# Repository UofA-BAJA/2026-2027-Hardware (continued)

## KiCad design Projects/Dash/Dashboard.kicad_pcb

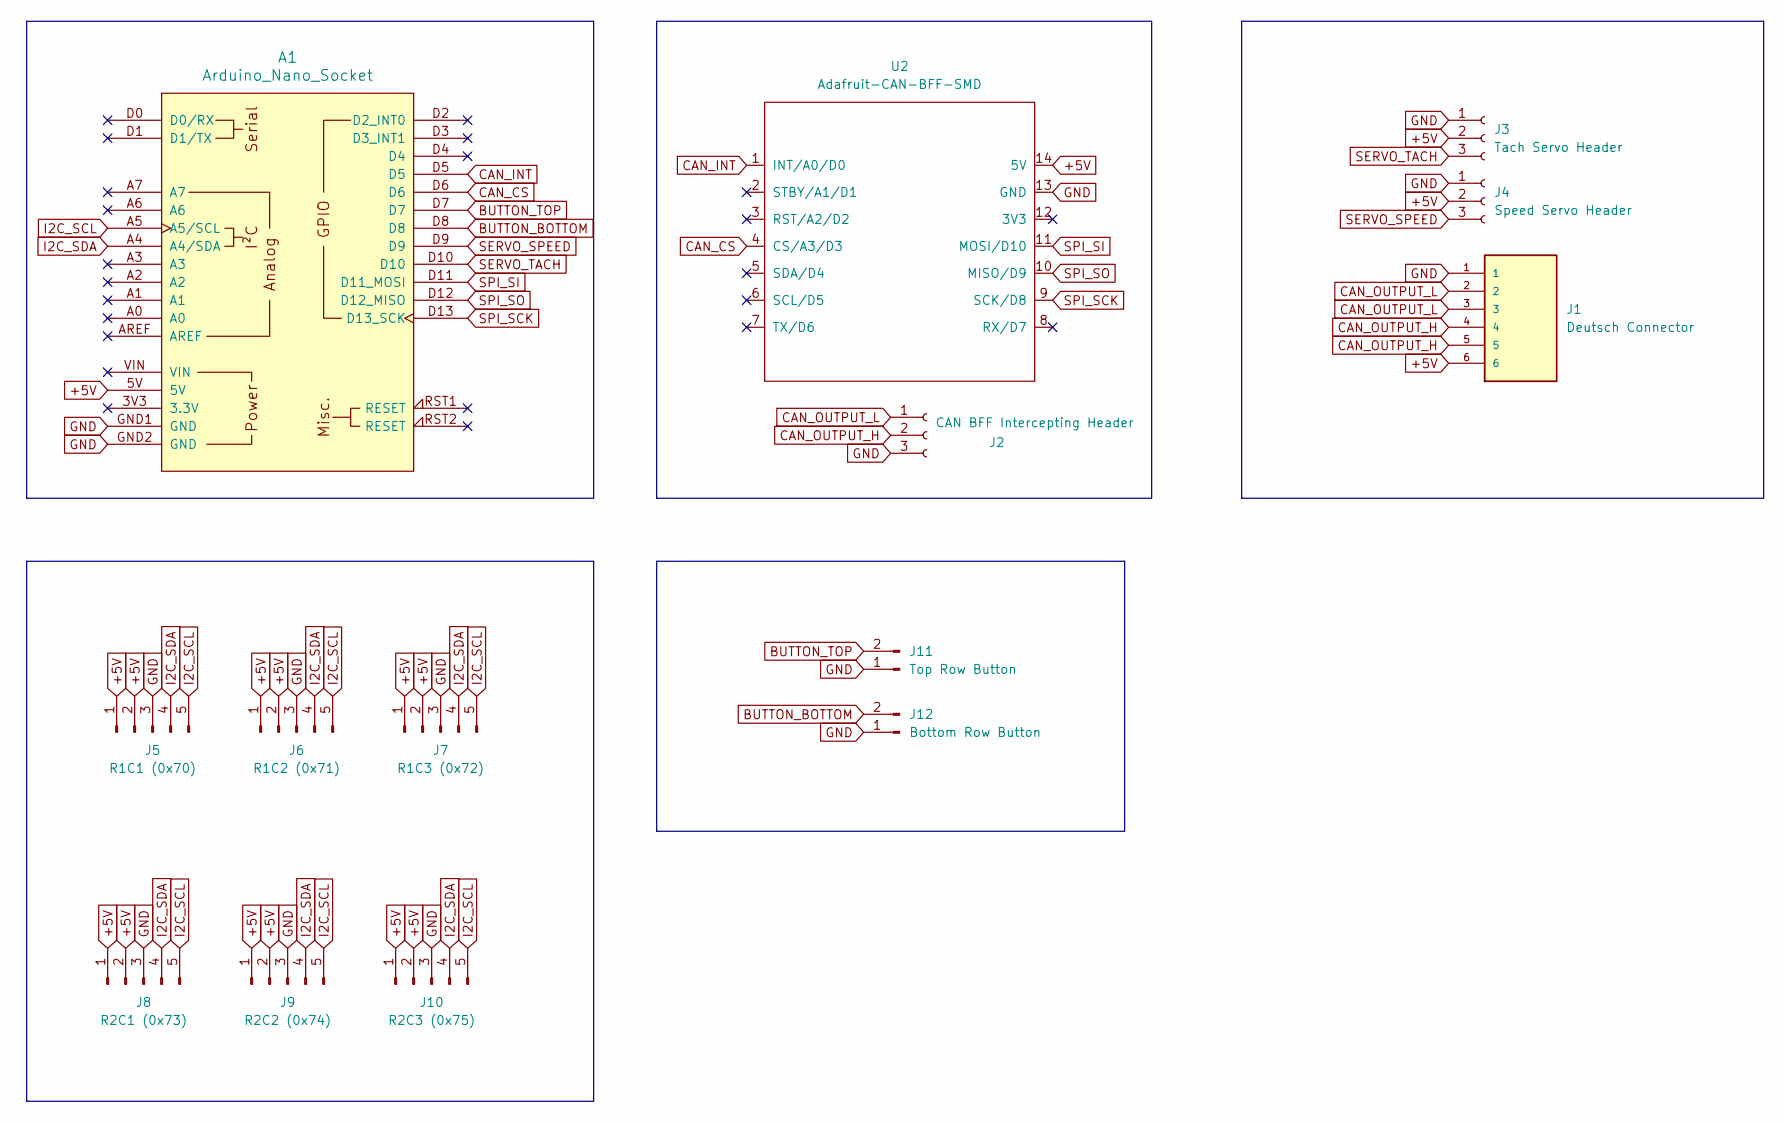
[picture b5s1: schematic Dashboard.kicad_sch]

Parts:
A1: Arduino_Nano_Socket
J1: Deutsch Connector; TE_DTF13-6P; PARTREV B
J2: CAN BFF Intercepting Header; PinHeader_1x03_P2.54mm_Vertical
J3: Tach Servo Header; PinHeader_1x03_P2.54mm_Vertical
J4: Speed Servo Header; PinHeader_1x03_P2.54mm_Vertical
J5: R1C1 (0x70); PinHeader_1x05_P2.54mm_Vertical
J6: R1C2 (0x71); PinHeader_1x05_P2.54mm_Vertical
J7: R1C3 (0x72); PinHeader_1x05_P2.54mm_Vertical
J8: R2C1 (0x73); PinHeader_1x05_P2.54mm_Vertical
J9: R2C2 (0x74); PinHeader_1x05_P2.54mm_Vertical
J10: R2C3 (0x75); PinHeader_1x05_P2.54mm_Vertical
J11: Top Row Button; PinHeader_1x02_P2.54mm_Vertical
J12: Bottom Row Button; PinHeader_1x02_P2.54mm_Vertical
U2: Adafruit-CAN-BFF-SMD

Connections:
+5V: A1.5V, J1.6, J3.2, J4.2, J5.1, J5.2, J6.1, J6.2, J7.1, J7.2, J8.1, J8.2, J9.1, J9.2, J10.1, J10.2, U2.14 (5V)
BUTTON_BOTTOM: A1.D8, J12.2
BUTTON_TOP: A1.D7, J11.2
CAN_CS: A1.D6, U2.4 (CS/A3/D3)
CAN_INT: A1.D5, U2.1 (INT/A0/D0)
CAN_OUTPUT_H: J1.4, J1.5, J2.2
CAN_OUTPUT_L: J1.2, J1.3, J2.1
GND: A1.GND1 (GND), A1.GND2 (GND), J1.1, J2.3, J3.1, J4.1, J5.3, J6.3, J7.3, J8.3, J9.3, J10.3, J11.1, J12.1, U2.13 (GND)
I2C_SCL: A1.A5 (A5/SCL), J5.5, J6.5, J7.5, J8.5, J9.5, J10.5
I2C_SDA: A1.A4 (A4/SDA), J5.4, J6.4, J7.4, J8.4, J9.4, J10.4
SERVO_SPEED: A1.D9, J4.3
SERVO_TACH: A1.D10, J3.3
SPI_SCK: A1.D13 (D13_SCK), U2.9 (SCK/D8)
SPI_SI: A1.D11 (D11_MOSI), U2.11 (MOSI/D10)
SPI_SO: A1.D12 (D12_MISO), U2.10 (MISO/D9)

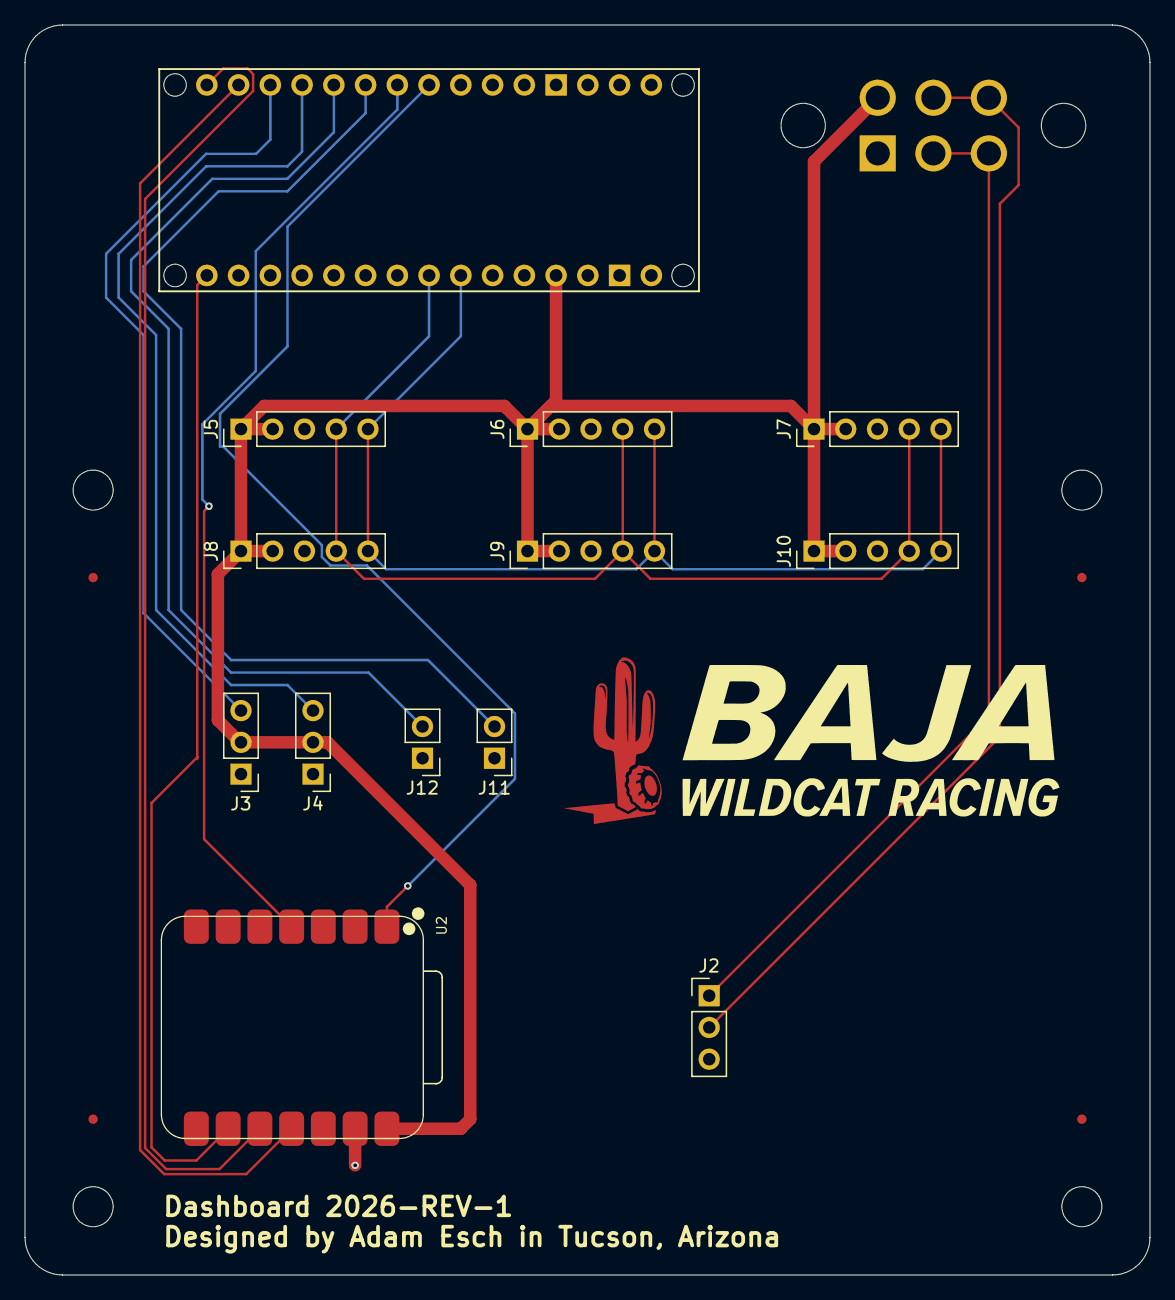
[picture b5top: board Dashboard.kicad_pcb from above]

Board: 2 copper layers, 90.0 x 100.0 mm, 14 parts (1 on the bottom side), 15 nets.

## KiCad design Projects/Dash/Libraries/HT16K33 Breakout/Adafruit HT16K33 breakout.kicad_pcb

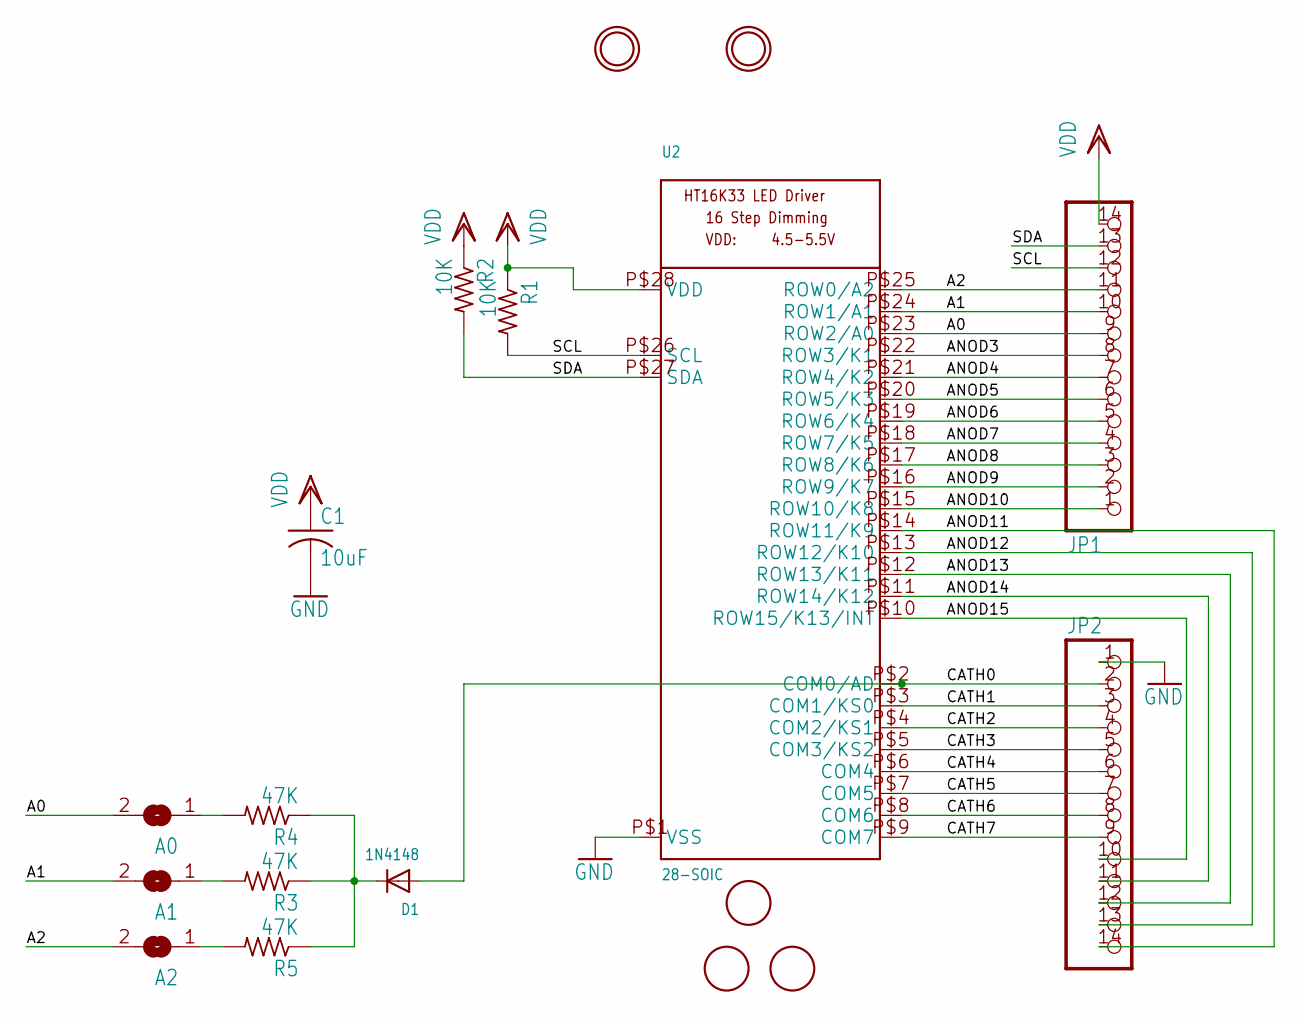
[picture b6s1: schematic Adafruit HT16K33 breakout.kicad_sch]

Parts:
A0, A1, A2: SOLDERJUMPERREFLOW_NOPASTE; SOLDERJUMPER_REFLOW_NOPASTE
C1: 10uF; C0805
D1: 1N4148; SOD-323F
JP1, JP2: PINHD-1X14-CB; 1X14-CB
R1, R2: 10K; R0805
R3, R4, R5: 47K; R0805
U2: 28-SOIC; SOP28_300MIL
U$1, U$2, U$6: FIDUCIAL; FIDUCIAL_1MM
U$4, U$5: MOUNTINGHOLE2.5; MOUNTINGHOLE_2.5_PLATED

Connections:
A0: A0.2, JP1.9, U2.P$23 (ROW2/A0)
A1: A1.2, JP1.10, U2.P$24 (ROW1/A1)
A2: A2.2, JP1.11, U2.P$25 (ROW0/A2)
ANOD3: JP1.8, U2.P$22 (ROW3/K1)
ANOD4: JP1.7, U2.P$21 (ROW4/K2)
ANOD5: JP1.6, U2.P$20 (ROW5/K3)
ANOD6: JP1.5, U2.P$19 (ROW6/K4)
ANOD7: JP1.4, U2.P$18 (ROW7/K5)
ANOD8: JP1.3, U2.P$17 (ROW8/K6)
ANOD9: JP1.2, U2.P$16 (ROW9/K7)
ANOD10: JP1.1, U2.P$15 (ROW10/K8)
ANOD11: JP2.14, U2.P$14 (ROW11/K9)
ANOD12: JP2.13, U2.P$13 (ROW12/K10)
ANOD13: JP2.12, U2.P$12 (ROW13/K11)
ANOD14: JP2.11, U2.P$11 (ROW14/K12)
ANOD15: JP2.10, U2.P$10 (ROW15/K13/INT)
CATH0: D1.A, JP2.2, U2.P$2 (COM0/AD)
CATH1: JP2.3, U2.P$3 (COM1/KS0)
CATH2: JP2.4, U2.P$4 (COM2/KS1)
CATH3: JP2.5, U2.P$5 (COM3/KS2)
CATH4: JP2.6, U2.P$6 (COM4)
CATH5: JP2.7, U2.P$7 (COM5)
CATH6: JP2.8, U2.P$8 (COM6)
CATH7: JP2.9, U2.P$9 (COM7)
GND: C1.2, JP2.1, U2.P$1 (VSS)
unnamed: A2.1, R5.2
unnamed: D1.C, R3.1, R4.1, R5.1
unnamed: A1.1, R3.2
unnamed: A0.1, R4.2
SCL: JP1.12, R1.2, U2.P$26 (SCL)
SDA: JP1.13, R2.2, U2.P$27 (SDA)
VDD: C1.1, JP1.14, R1.1, R2.1, U2.P$28 (VDD)

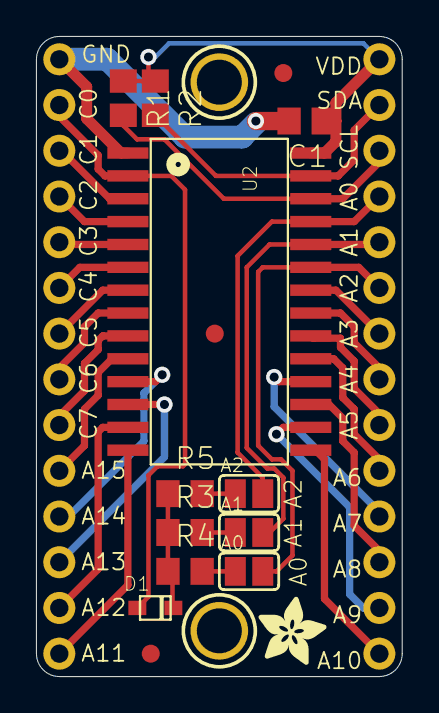
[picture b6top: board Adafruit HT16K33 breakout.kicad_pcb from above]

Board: 16 copper layers, 20.3 x 35.6 mm, 20 parts (1 on the bottom side), 32 nets.

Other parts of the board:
U$3: ADAFRUIT_3.5MM
U$7: ADAFRUIT_5MM
